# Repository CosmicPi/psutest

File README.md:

# psutest
Power supply test for Cockcroft Walton converter
Hardware tested and working as expected with a Digital Multi-Meter, need to check it with a scope. It is designed to work with the Ketek [PM3325 SiPM](https://www.ketek.net/wp-content/uploads/2018/12/KETEK-PM3325-WB-D0-Datasheet.pdf) module. In the meantime check out the LTSpice model!

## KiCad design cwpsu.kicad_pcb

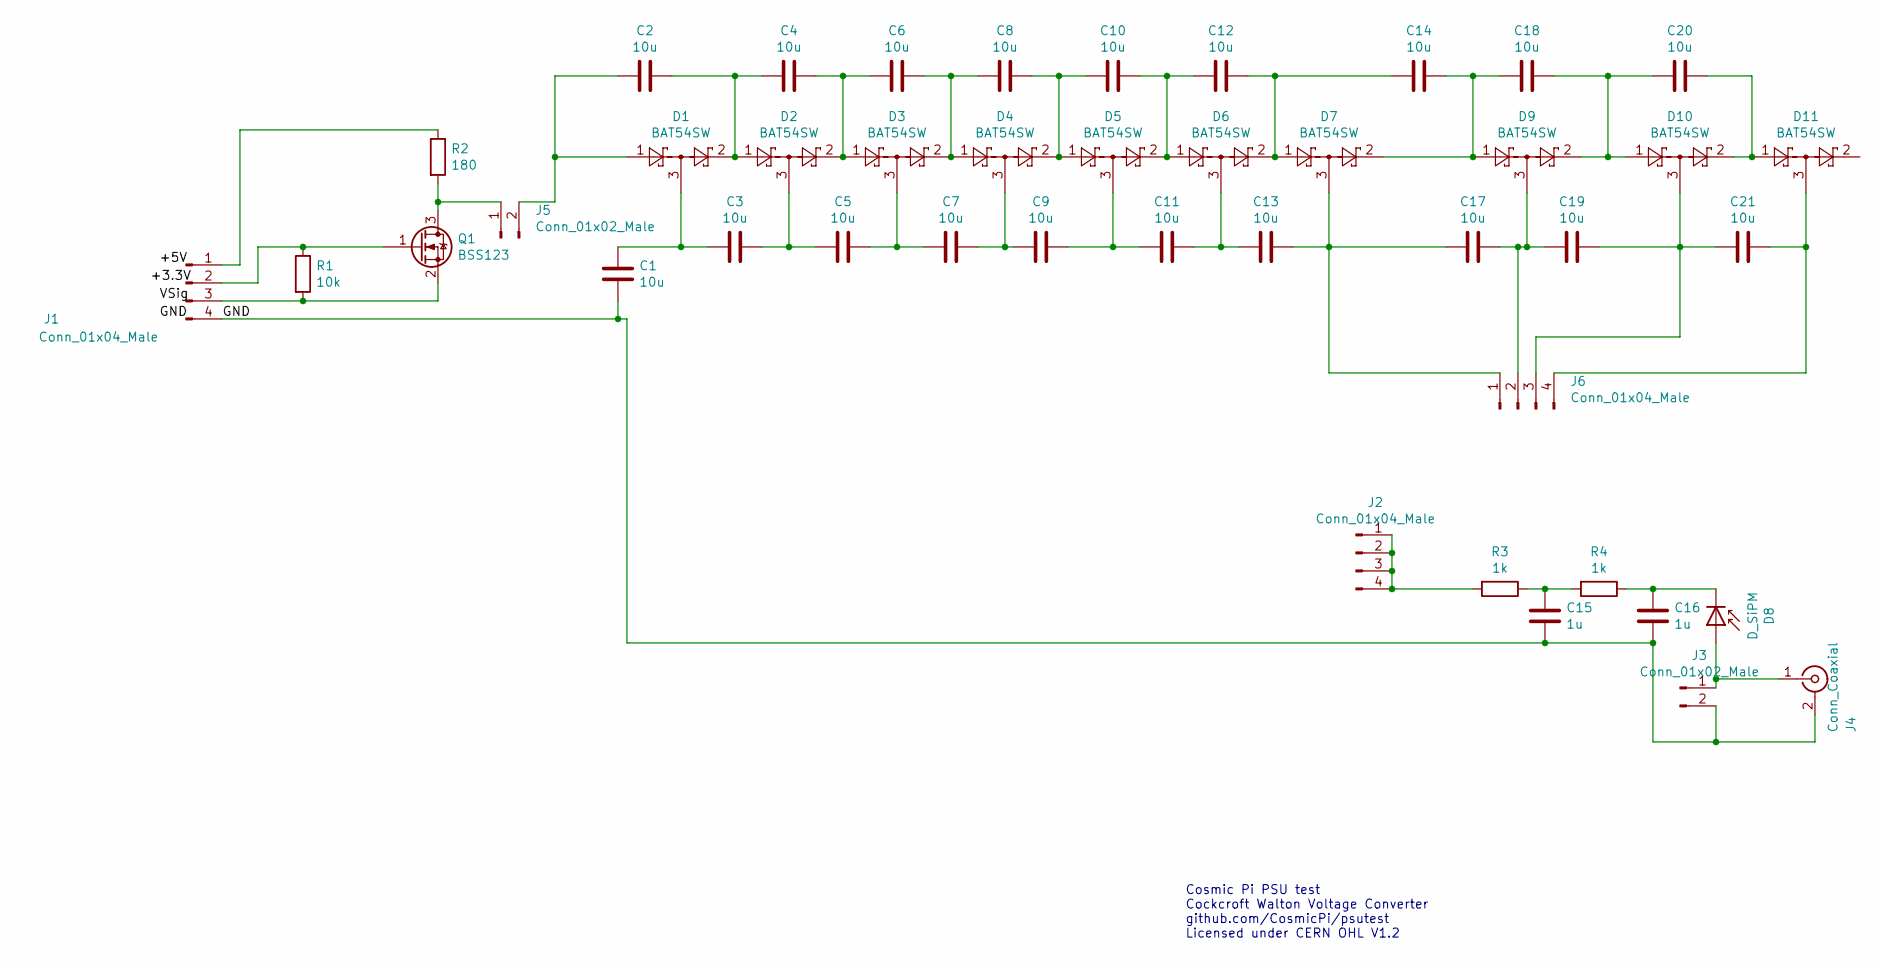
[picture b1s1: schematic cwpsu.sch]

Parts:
C1, C2, C3, C4, C5, C6, C7, C8, C9, C10, C11, C12, C13, C14, C17, C18, C19, C20, C21: 10u; C_0603_1608Metric
C15, C16: 1u; C_0603_1608Metric
D1, D2, D3, D4, D5, D6, D7, D9, D10, D11: BAT54SW; SOT-323_SC-70
D8: D_SiPM; Ketek_PM3325-WB
J1, J2, J6: Conn_01x04_Male; PinSocket_1x04_P2.54mm_Vertical
J3, J5: Conn_01x02_Male; PinSocket_1x02_P2.54mm_Vertical
J4: Conn_Coaxial; SMA_Molex_73251-1153_EdgeMount_Horizontal
Q1: BSS123; SOT-23
R1: 10k; R_0603_1608Metric
R2: 180; R_0603_1608Metric
R3, R4: 1k; R_0603_1608Metric

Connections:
/GND: C1.1, C15.1, C16.1, J1.4, J3.2, J4.2 (Ext)
unnamed: C1.2, C3.2, D1.3
unnamed: C2.1, C4.2, D1.2, D2.1
unnamed: C2.2, D1.1, J5.2
unnamed: C3.1, C5.2, D2.3
unnamed: C4.1, C6.2, D2.2, D3.1
unnamed: C5.1, C7.2, D3.3
unnamed: C6.1, C8.2, D3.2, D4.1
unnamed: C7.1, C9.2, D4.3
unnamed: C10.1, C12.2, D5.2, D6.1
unnamed: C8.1, C10.2, D4.2, D5.1
unnamed: C11.1, C13.2, D6.3
unnamed: C9.1, C11.2, D5.3
unnamed: C12.1, C14.2, D6.2, D7.1
unnamed: C13.1, C17.2, D7.3, J6.1
unnamed: C14.1, C18.2, D7.2, D9.1
unnamed: C15.2, R3.1, R4.2
unnamed: C16.2, D8.1 (K), R4.1
unnamed: C17.1, C19.2, D9.3, J6.2
unnamed: C18.1, C20.2, D9.2, D10.1
unnamed: C19.1, C21.2, D10.3, J6.3
unnamed: C20.1, D10.2, D11.1
unnamed: C21.1, D11.3, J6.4
unnamed: D8.2 (A), J3.1, J4.1 (In)
unnamed: J1.1, R2.1
unnamed: J1.2, Q1.1 (G), R1.1
unnamed: J1.3, Q1.2 (S), R1.2
unnamed: J2.1, J2.2, J2.3, J2.4, R3.2
unnamed: J5.1, Q1.3 (D), R2.2

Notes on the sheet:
Cosmic Pi PSU test Cockcroft Walton Voltage Converter github.com/CosmicPi/psutest Licensed under CERN OHL V1.2

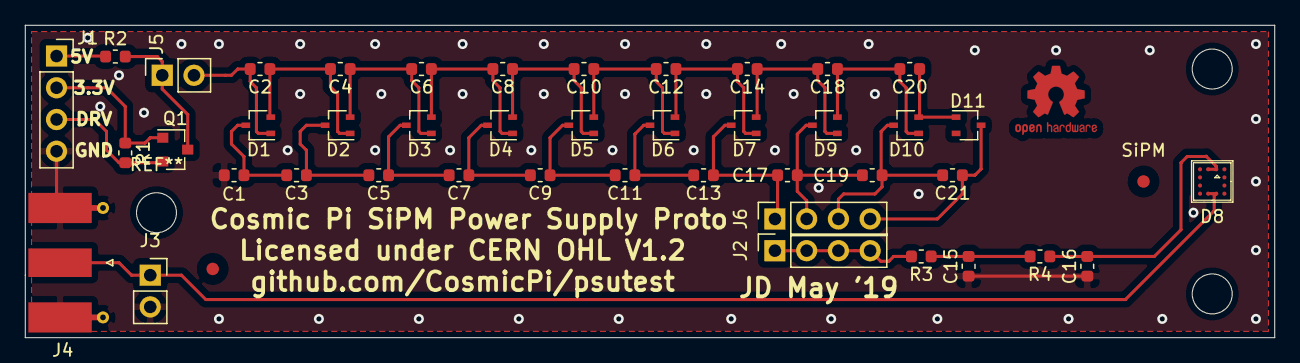
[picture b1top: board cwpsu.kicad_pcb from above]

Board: 2 copper layers, 100.0 x 25.0 mm, 45 parts (0 on the bottom side), 29 nets.

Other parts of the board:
Input: Fiducial_1mm_Dia_2.54mm_Outer_CopperTop
SiPM: Fiducial_1mm_Dia_2.54mm_Outer_CopperTop

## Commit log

2019-05-12 Kicad files upload
2019-05-12 Spice simulation file
    Target voltage is about 27 volts.
2019-05-13 3d view
2019-05-13 cropped
2019-06-02 Added photo of the hardware and first test results
